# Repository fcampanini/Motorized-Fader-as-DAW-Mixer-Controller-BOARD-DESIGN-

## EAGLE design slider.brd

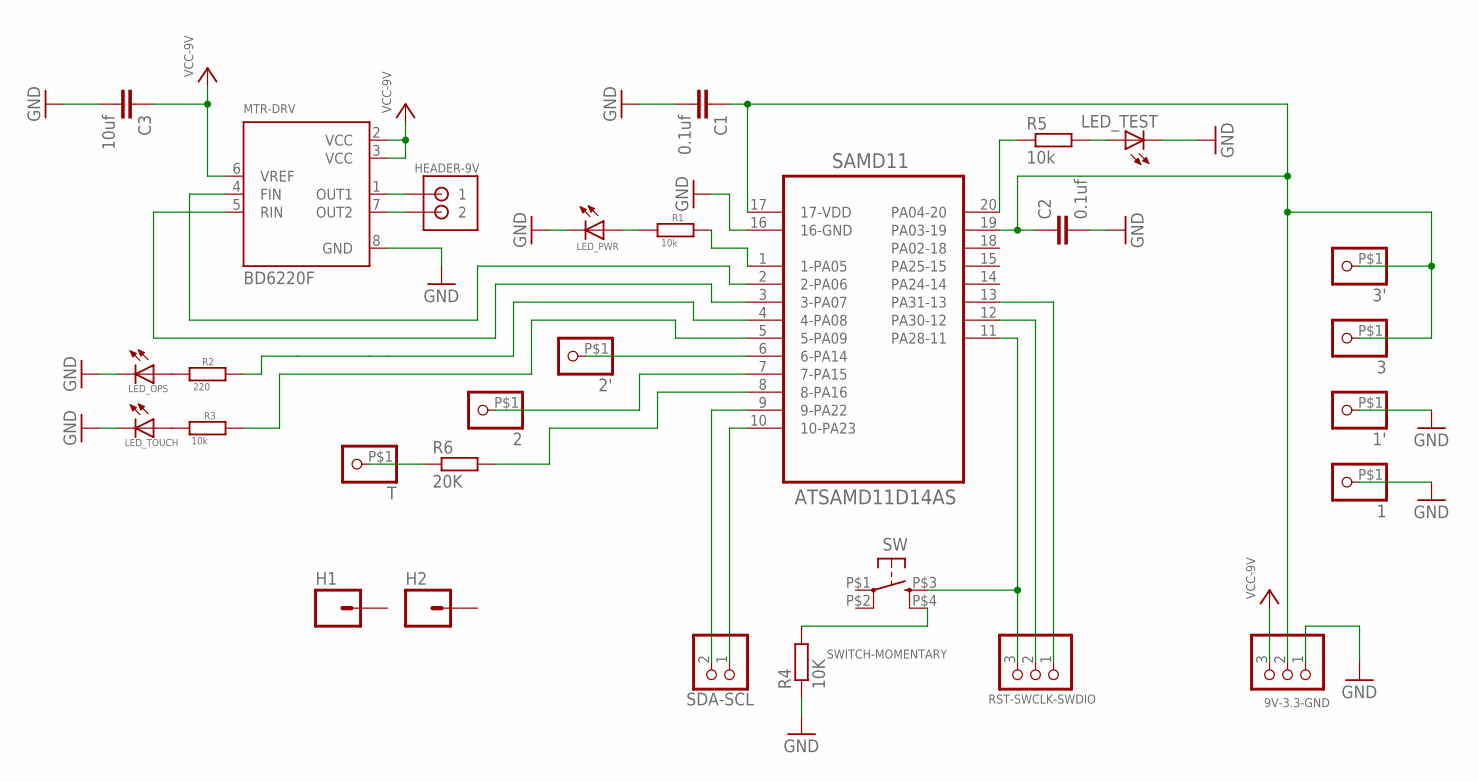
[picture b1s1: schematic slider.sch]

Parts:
1, 1', 2, 2', 3, 3': PINHD-1X1; 1X01
9V-3.3-GND: PINHD-1X3; 1X03
C1, C2: 0.1uf; C0805
C3: 10uf; C0805
H1, H2: M01PTH_2MM; 1X01_2MM
HEADER-9V: JST-PH_2-PIN_HEADER; JST_B2B-PH_HEADER
LED_OPS: LEDCHIP-LED0805; CHIP-LED0805
LED_PWR: LEDCHIP-LED0805; CHIP-LED0805
LED_TEST: LEDCHIP-LED0805; CHIP-LED0805
LED_TOUCH: LEDCHIP-LED0805; CHIP-LED0805
MTR-DRV: BD6220F; SOP8
R1, R3, R5: 10k; R0805
R2: 220; R0805
R4: 10K; R0805
R6: 20K; R0805
RST-SWCLK-SWDIO: PINHD-1X3; 1X03
SAMD11: ATSAMD11D14AS; SOIC20
SDA-SCL: PINHD-1X2; 1X02
SW: SWITCH-MOMENTARY
T: PINHD-1X1; 1X01

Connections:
GND: 1.P$1, 1'.P$1, 9V-3.3-GND.1, C1.2, C2.2, C3.2, LED_OPS.C, LED_PWR.C, LED_TEST.C, LED_TOUCH.C, MTR-DRV.8 (GND), R4.1, SAMD11.16 (16-GND)
unnamed: R5.1, SAMD11.20 (PA04-20)
unnamed: 3.P$1, 3'.P$1, 9V-3.3-GND.2, C1.1, C2.1, SAMD11.17 (17-VDD), SAMD11.19 (PA03-19)
unnamed: HEADER-9V.P1 (1), MTR-DRV.1 (OUT1)
unnamed: HEADER-9V.P2 (2), MTR-DRV.7 (OUT2)
unnamed: LED_PWR.A, R1.1
unnamed: R1.2, SAMD11.1 (1-PA05)
unnamed: MTR-DRV.4 (FIN), SAMD11.2 (2-PA06)
unnamed: MTR-DRV.5 (RIN), SAMD11.3 (3-PA07)
unnamed: LED_OPS.A, R2.1
unnamed: R2.2, SAMD11.4 (4-PA08)
unnamed: R3.2, SAMD11.5 (5-PA09)
unnamed: LED_TOUCH.A, R3.1
unnamed: R6.1, T.P$1
unnamed: 2'.P$1, SAMD11.6 (6-PA14)
unnamed: 2.P$1, SAMD11.7 (7-PA15)
unnamed: SAMD11.9 (9-PA22), SDA-SCL.2
unnamed: R6.2, SAMD11.8 (8-PA16)
unnamed: SAMD11.10 (10-PA23), SDA-SCL.1
unnamed: RST-SWCLK-SWDIO.3, SAMD11.11 (PA28-11), SW.P$3 (3)
unnamed: RST-SWCLK-SWDIO.2, SAMD11.12 (PA30-12)
unnamed: RST-SWCLK-SWDIO.1, SAMD11.13 (PA31-13)
unnamed: R4.2, SW.P$4 (4)
unnamed: LED_TEST.A, R5.2
VCC: 9V-3.3-GND.3, C3.1, MTR-DRV.2 (VCC), MTR-DRV.3 (VCC), MTR-DRV.6 (VREF)

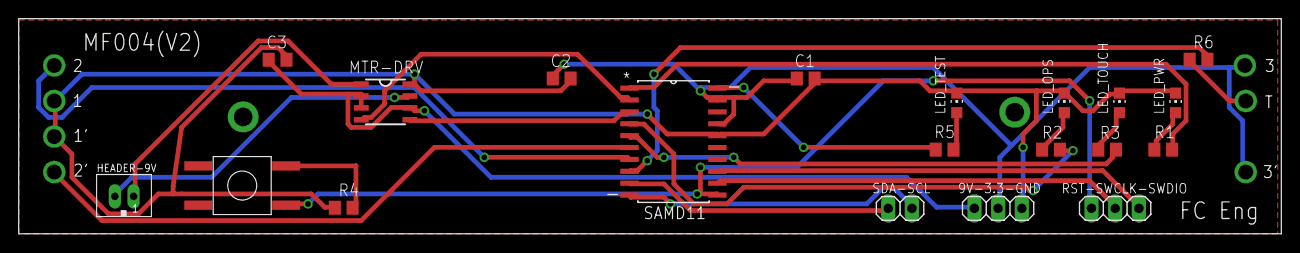
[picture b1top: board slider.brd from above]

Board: 2 copper layers, 135.0 x 23.0 mm, 29 parts (0 on the bottom side), 25 nets.

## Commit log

2020-12-18 Version 1.0

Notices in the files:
parts and their libraries:
SparkFun-Connectors: Licensing: Creative Commons ShareAlike 4.0 International - https://creativecommons.org/licenses/by-sa/4.0
